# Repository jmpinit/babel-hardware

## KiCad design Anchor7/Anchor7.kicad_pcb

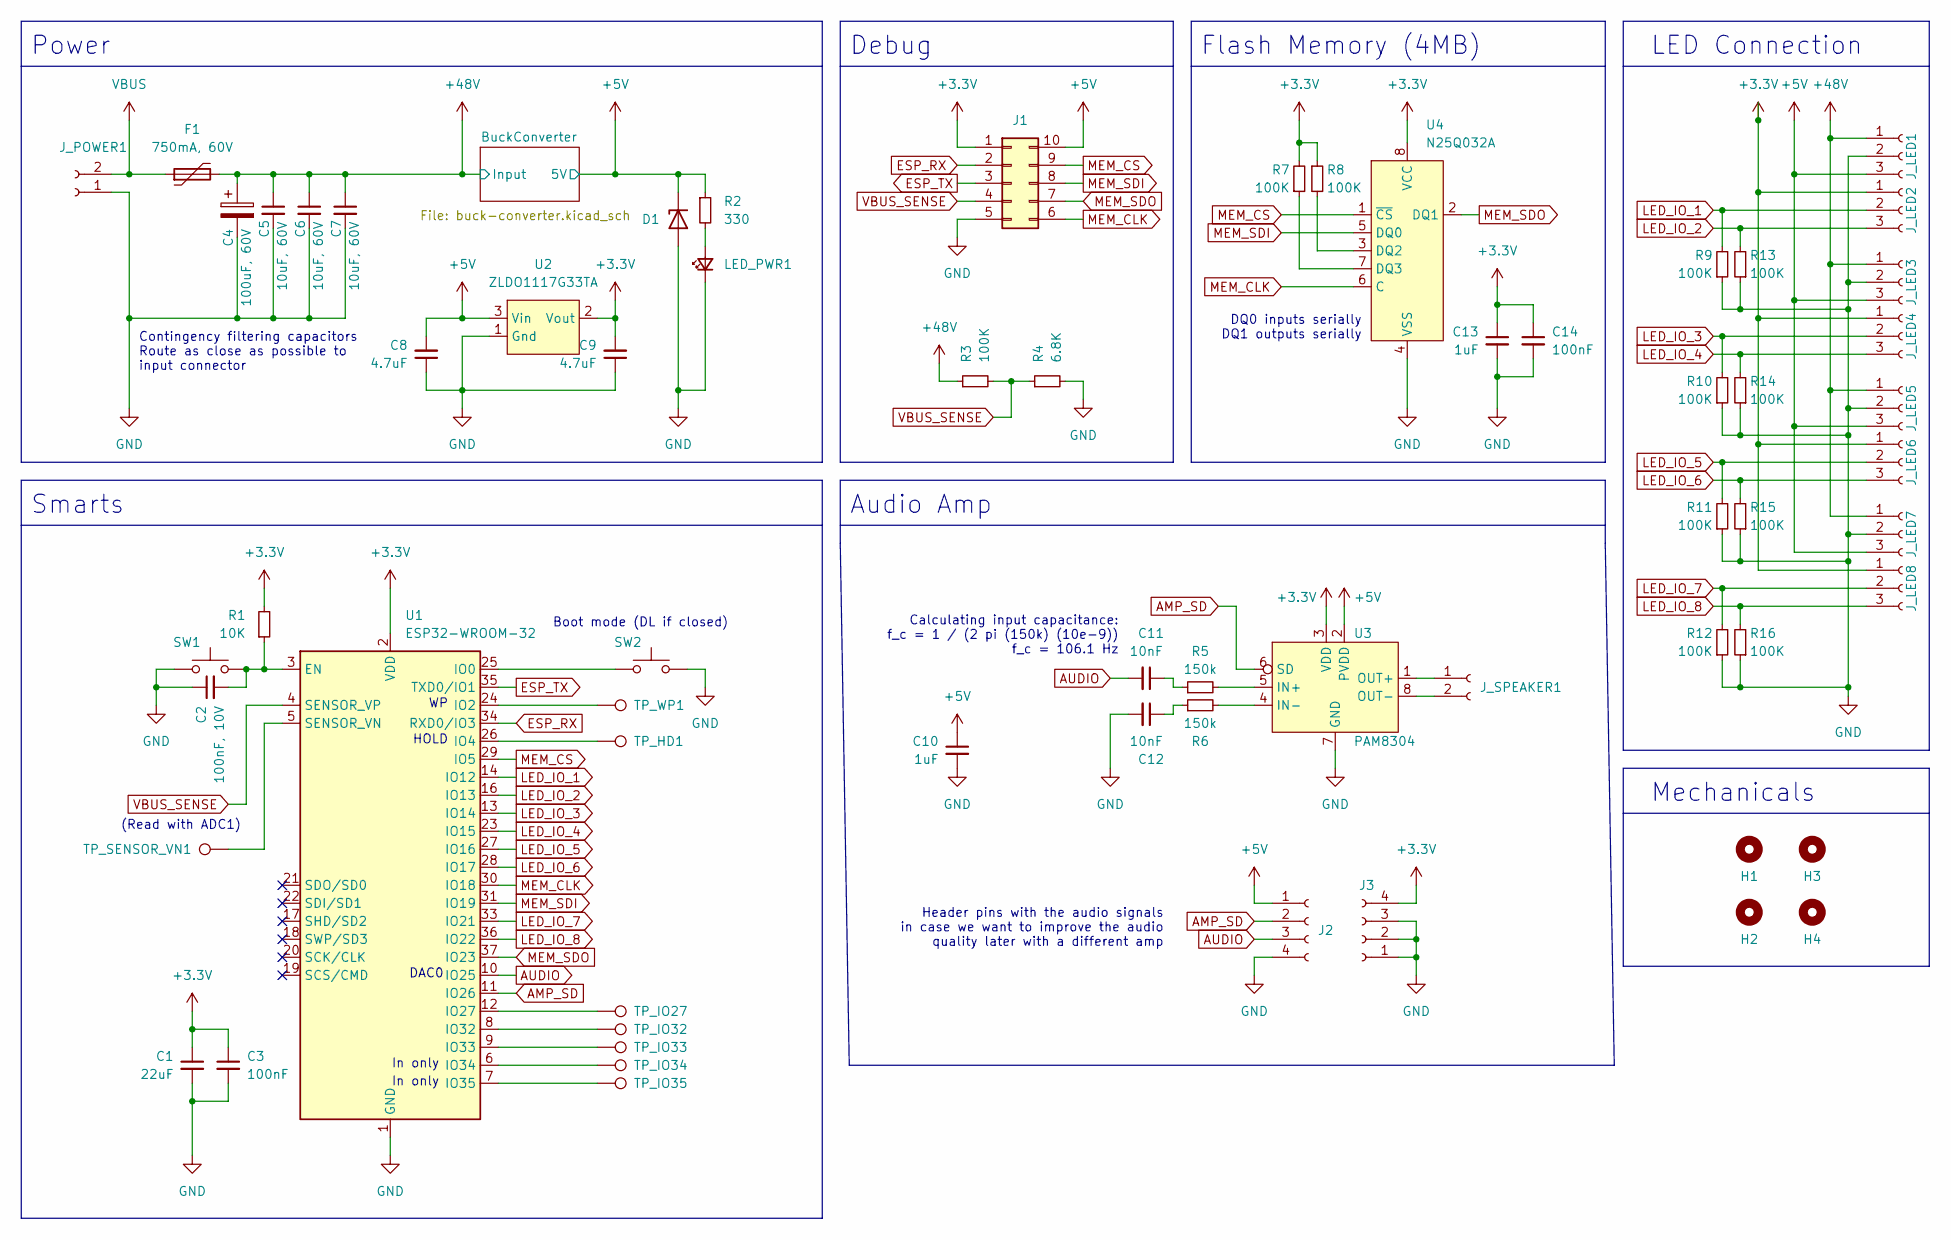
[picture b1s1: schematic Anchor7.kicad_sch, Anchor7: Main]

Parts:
C1: 22uF; C_0603_1608Metric; Digi-Key Part Number 1276-1274-2-ND
C2: 100nF, 10V; C_0402_1005Metric; Digi-Key Part Number 1276-1043-2-ND
C3, C14: 100nF; C_0402_1005Metric; Digi-Key Part Number 1276-1043-2-ND
C4: 100uF, 60V; CP_Radial_D8.0mm_P3.50mm
C5, C6, C7: 10uF, 60V; C_1206_3216Metric; Digi-Key Part Number 1276-7053-2-ND
C8, C9: 4.7uF; C_0603_1608Metric; Digi-Key Part Number 1276-1044-2-ND
C10, C13: 1uF; C_0603_1608Metric; Digi-Key Part Number 1276-1945-2-ND
C11, C12: 10nF; C_0402_1005Metric; Digi-Key Part Number 478-1114-2-ND
D1: 5.1V; SOT-23; Digi-Key Part Number 1727-2939-2-ND
F1: 750mA, 60V; Fuse_2920_7451Metric_Pad2.10x5.45mm_HandSolder; Digi-Key Part Number 507-1743-2-ND
H1, H2, H3, H4: MountingHole; MountingHole_3.2mm_M3
J1: Conn_02x05_Counter_Clockwise; Tag-Connect_TC2050-IDC-FP_2x05_P1.27mm_Vertical
J2, J3: Conn_01x04_Female; PinHeader_1x04_P2.54mm_Vertical
J_LED1, J_LED2, J_LED3, J_LED4, J_LED5, J_LED6, J_LED7, J_LED8: Conn_01x03_Female; PinHeader_1x03_P2.54mm_Vertical
J_POWER1: Conn_01x02_Female; Anchor_Power_2Pad
J_SPEAKER1: Conn_01x02_Female; PinHeader_1x02_P2.54mm_Vertical
LED_PWR1: LED_Small; LED_0402_1005Metric_Pad0.77x0.64mm_HandSolder
R1: 10K; R_0402_1005Metric; Digi-Key Part Number CR0402-JW-103GLFTR-ND
R2: 330; R_0402_1005Metric; Digi-Key Part Number 1292-WR04X331JTLTR-ND
R3, R7, R8, R9, R10, R11, R12, R13, R14, R15, R16: 100K; R_0402_1005Metric; Digi-Key Part Number 1292-WR04X104JTLTR-ND
R4: 6.8K; R_0402_1005Metric; Digi-Key Part Number 1292-WR04X682JTLTR-ND
R5, R6: 150k; R_0402_1005Metric; Digi-Key Part Number 1292-WR04X154JTLTR-ND
SW1, SW2: SW_Push; SW_SPST_PTS526; Digi-Key Part Number CKN12220-1-ND
TP_HD1: TestPoint; TestPoint_Pad_D1.5mm
TP_IO27, TP_IO32, TP_IO33, TP_IO34, TP_IO35: TestPoint; TestPoint_Pad_D1.5mm
TP_SENSOR_VN1: TestPoint; TestPoint_Pad_D1.5mm
TP_WP1: TestPoint; TestPoint_Pad_D1.5mm
U1: ESP32-WROOM-32
U2: ZLDO1117G33TA; SOT-223-3_TabPin2; Digi-Key Part Number ZLDO1117G33DITR-ND
U3: PAM8304; DFN-8-1EP_3x3mm_P0.65mm_EP1.55x2.4mm; Digi-Key Part Number PAM8304AYRDITR-ND
U4: N25Q032A; SOIC-8_3.9x4.9mm_P1.27mm; Digi-Key Part Number 1450-N25Q032A13ESC40FTR-ND

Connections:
+3V3: C1.1, C3.1, C9.2, C13.1, C14.1, J1.1, J3.4, J_LED2.1, J_LED4.1, J_LED6.1, J_LED8.1, R1.2, R7.2, R8.1, U1.2 (VDD), U2.2 (Vout), U3.3 (VDD), U4.8 (VCC)
+5V: C8.2, C10.1, D1.1 (K), J1.10, J2.1, J_LED1.3, J_LED3.3, J_LED5.3, J_LED7.3, R2.1, U2.3 (Vin), U3.2 (PVDD); also elsewhere on the board
+48V: C4.1, C5.1, C6.1, C7.1, F1.2, J_LED1.1, J_LED3.1, J_LED5.1, J_LED7.1, R3.1; also elsewhere on the board
AMP_SD: J2.2, U1.11 (IO26), U3.6 (SD)
AUDIO: C11.2, J2.3, U1.10 (IO25)
ESP_RX: J1.2, U1.34 (RXD0/IO3)
ESP_TX: J1.3, U1.35 (TXD0/IO1)
GND: C1.2, C2.1, C3.2, C4.2, C5.2, C6.2, C7.2, C8.1, C9.1, C10.2, C12.2, C13.2, C14.2, D1.2 (A), J1.5, J2.4, J3.1, J3.2, J3.3, J_LED1.2, J_LED3.2, J_LED5.2, J_LED7.2, J_POWER1.1, LED_PWR1.1 (K), R4.2, R9.1, R10.1, R11.1, R12.1, R13.1, R14.1, R15.1, R16.1, SW1.1, SW2.2, U1.1 (GND), U1.15 (GND), U1.38 (GND), U1.39 (GND), U2.1 (Gnd), U3.7 (GND), U4.4 (VSS); also elsewhere on the board
LED_IO_1: J_LED2.2, R9.2, U1.14 (IO12)
LED_IO_2: J_LED2.3, R13.2, U1.16 (IO13)
LED_IO_3: J_LED4.2, R10.2, U1.13 (IO14)
LED_IO_4: J_LED4.3, R14.2, U1.23 (IO15)
LED_IO_5: J_LED6.2, R11.2, U1.27 (IO16)
LED_IO_6: J_LED6.3, R15.2, U1.28 (IO17)
LED_IO_7: J_LED8.2, R12.2, U1.33 (IO21)
LED_IO_8: J_LED8.3, R16.2, U1.36 (IO22)
MEM_CLK: J1.6, U1.30 (IO18), U4.6 (C)
MEM_CS: J1.9, U1.29 (IO5), U4.1 (~CS)
MEM_SDI: J1.8, U1.31 (IO19), U4.5 (DQ0)
MEM_SDO: J1.7, U1.37 (IO23), U4.2 (DQ1)
unnamed: C2.2, R1.1, SW1.2, U1.3 (EN)
unnamed: C11.1, R5.1
unnamed: C12.1, R6.1
unnamed: J_SPEAKER1.1, U3.1 (OUT+)
unnamed: J_SPEAKER1.2, U3.8 (OUT-)
unnamed: LED_PWR1.2 (A), R2.2
unnamed: R5.2, U3.5 (IN+)
unnamed: R6.2, U3.4 (IN-)
unnamed: R7.1, U4.7 (DQ3)
unnamed: R8.2, U4.3 (DQ2)
unnamed: SW2.1, U1.25 (IO0)
unnamed: TP_HD1.1, U1.26 (IO4)
unnamed: TP_IO27.1, U1.12 (IO27)
unnamed: TP_IO32.1, U1.8 (IO32)
unnamed: TP_IO33.1, U1.9 (IO33)
unnamed: TP_IO34.1, U1.6 (IO34)
unnamed: TP_IO35.1, U1.7 (IO35)
unnamed: TP_SENSOR_VN1.1, U1.5 (SENSOR_VN)
unnamed: TP_WP1.1, U1.24 (IO2)
VBUS: F1.1, J_POWER1.2
VBUS_SENSE: J1.4, R3.2, R4.1, U1.4 (SENSOR_VP)

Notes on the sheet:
Header pins with the audio signals in case we want to improve the audio quality later with a different amp
Power
(Read with ADC1)
Smarts
Audio Amp
HOLD
Mechanicals
Contingency filtering capacitors Route as close as possible to input connector
In only
LED Connection
Flash Memory (4MB)
DAC0
Debug
DQ0 inputs serially DQ1 outputs serially
Boot mode (DL if closed)
Calculating input capacitance: f_c = 1 / (2 pi (150k) (10e-9)) f_c = 106.1 Hz

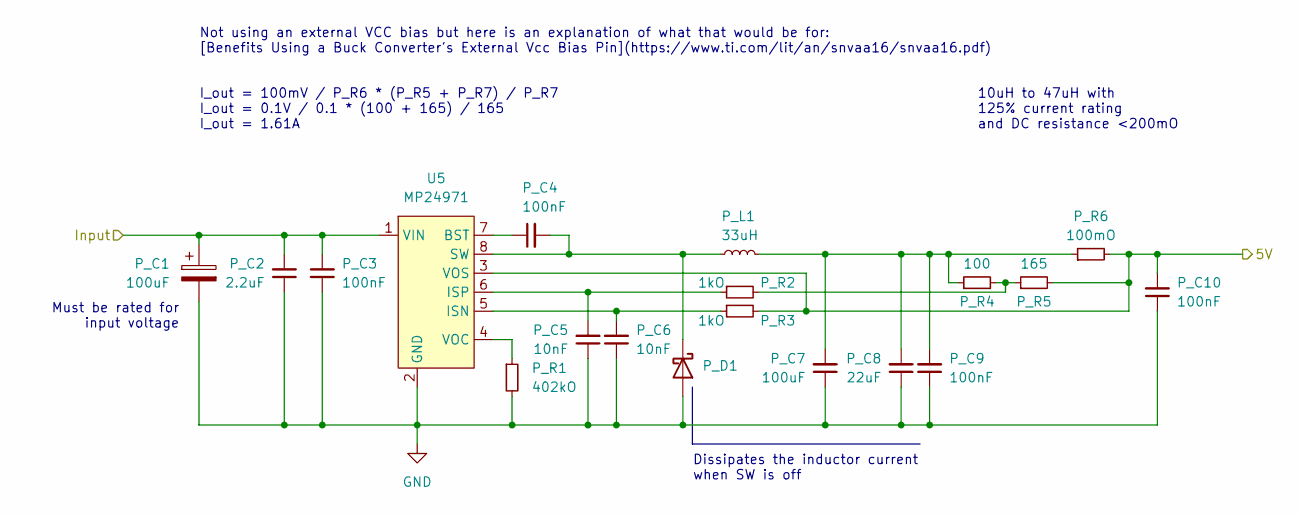
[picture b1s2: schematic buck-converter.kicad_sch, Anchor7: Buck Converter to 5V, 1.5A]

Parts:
P_C1: 100uF; CP_Radial_D8.0mm_P3.50mm; Digi-Key Part Number 1189-3041-ND
P_C2: 2.2uF; C_1206_3216Metric; Digi-Key Part Number 445-181654-2-ND
P_C3: 100nF; C_0805_2012Metric; Digi-Key Part Number 399-C0805C104KMREC7210TR-ND
P_C4, P_C9, P_C10: 100nF; C_0402_1005Metric; Digi-Key Part Number 1276-1004-2-ND
P_C5, P_C6: 10nF; C_0402_1005Metric; Digi-Key Part Number 478-04025C103MAT2ATR-ND
P_C7: 100uF; C_1210_3225Metric; Digi-Key Part Number 1276-1092-2-ND
P_C8: 22uF; C_0805_2012Metric; Digi-Key Part Number 490-10511-2-ND
P_D1: D_Schottky; D_SMA; Digi-Key Part Number 641-1102-2-ND
P_L1: 33uH; L_Taiyo-Yuden_NS-125xx; Digi-Key Part Number NS12555T330MN
P_R1: 402kO; R_0402_1005Metric; Digi-Key Part Number RMCF0402FT402KTR-ND
P_R2, P_R3: 1kO; R_0402_1005Metric; Digi-Key Part Number P1.0KJTR-ND
P_R4: 100; R_0402_1005Metric; Digi-Key Part Number CR0402-JW-101GLFTR-ND
P_R5: 165; R_0402_1005Metric; Digi-Key Part Number RMCF0402FT165RTR-ND
P_R6: 100mO; R_2512_6332Metric; Digi-Key Part Number CSRN2512FKR100TR-ND
U5: MP24971; SOIC-8-1EP_3.9x4.9mm_P1.27mm_EP2.29x3mm_ThermalVias; Digi-Key Part Number MP24971DN-LF-Z

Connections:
+5V: P_C10.2, P_R3.2, P_R5.2, P_R6.2, U5.3 (VOS); also elsewhere on the board
+48V: P_C1.1, P_C2.2, P_C3.2, U5.1 (VIN); also elsewhere on the board
GND: P_C1.2, P_C2.1, P_C3.1, P_C5.1, P_C6.1, P_C7.1, P_C8.1, P_C9.1, P_C10.1, P_D1.2 (A), P_R1.2, U5.2 (GND), U5.9 (GND); also elsewhere on the board
unnamed: P_C4.1, U5.7 (BST)
unnamed: P_C4.2, P_D1.1 (K), P_L1.1, U5.8 (SW)
unnamed: P_C5.2, P_R2.1, U5.6 (ISP)
unnamed: P_C6.2, P_R3.1, U5.5 (ISN)
unnamed: P_C7.2, P_C8.2, P_C9.2, P_L1.2, P_R4.1, P_R6.1
unnamed: P_R1.1, U5.4 (VOC)
unnamed: P_R2.2, P_R4.2, P_R5.1

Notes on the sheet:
10uH to 47uH with 125% current rating and DC resistance <200mO
Not using an external VCC bias but here is an explanation of what that would be for: [Benefits Using a Buck Converter's External Vcc Bias Pin](https://www.ti.com/lit/an/snvaa16/snvaa16.pdf)
Must be rated for input voltage
Dissipates the inductor current when SW is off
I_out = 100mV / P_R6 * (P_R5 + P_R7) / P_R7 I_out = 0.1V / 0.1 * (100 + 165) / 165 I_out = 1.61A

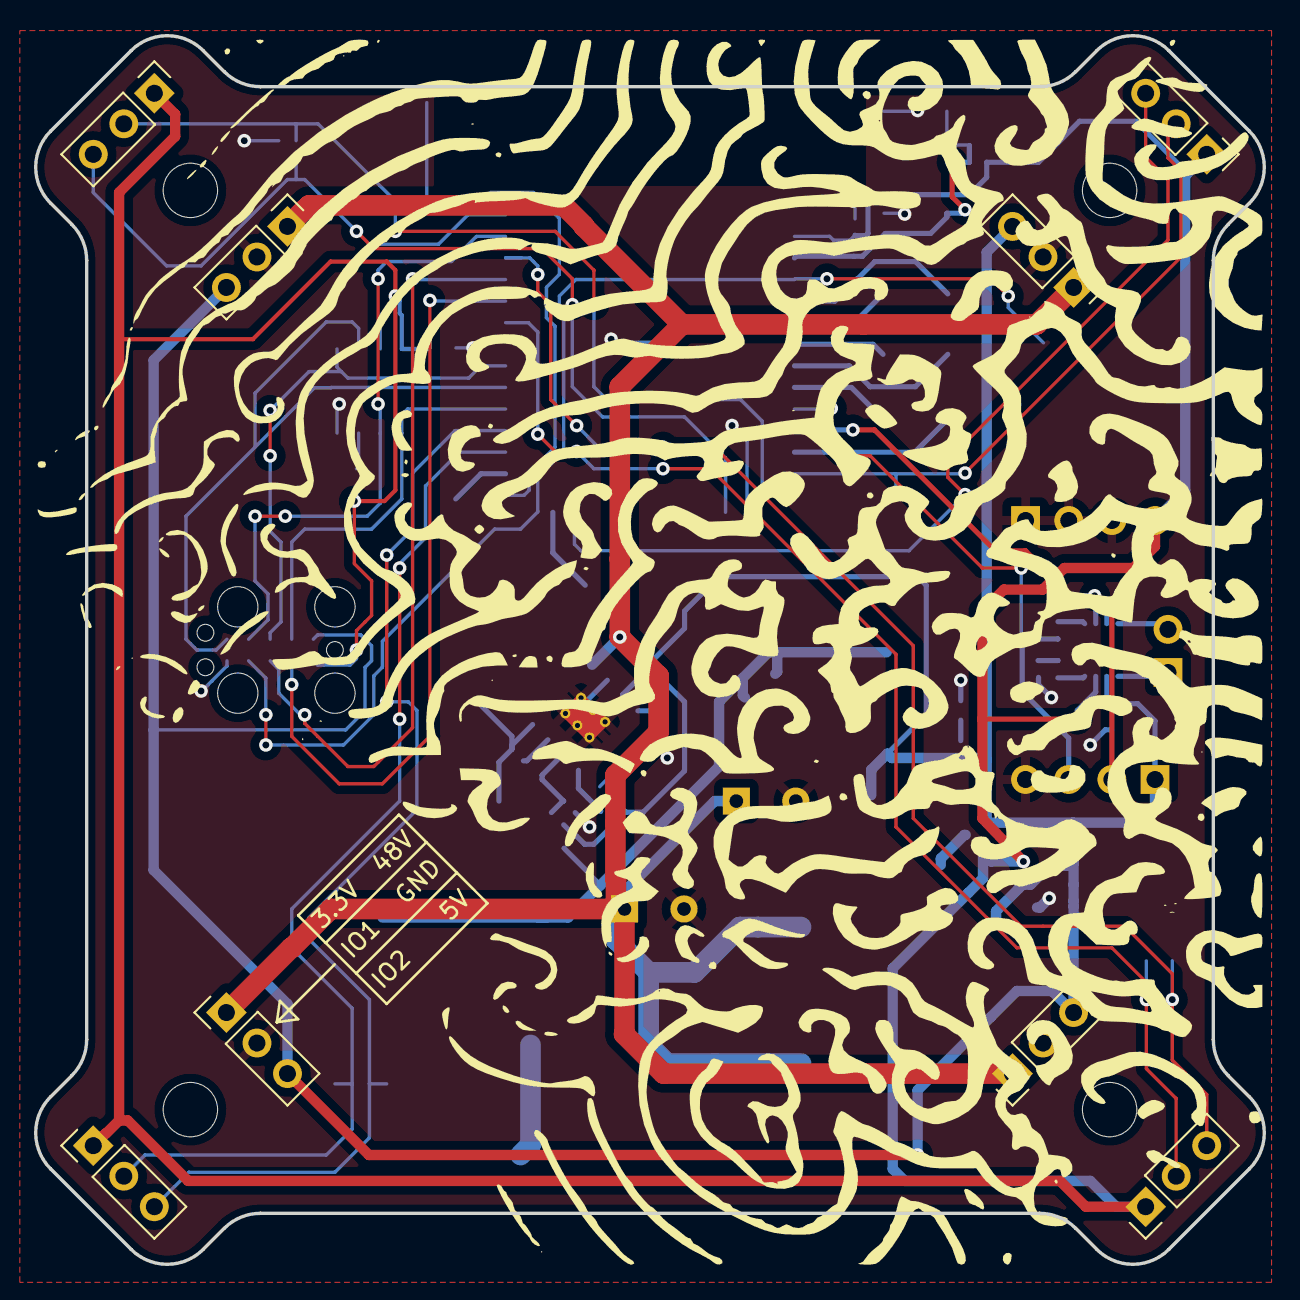
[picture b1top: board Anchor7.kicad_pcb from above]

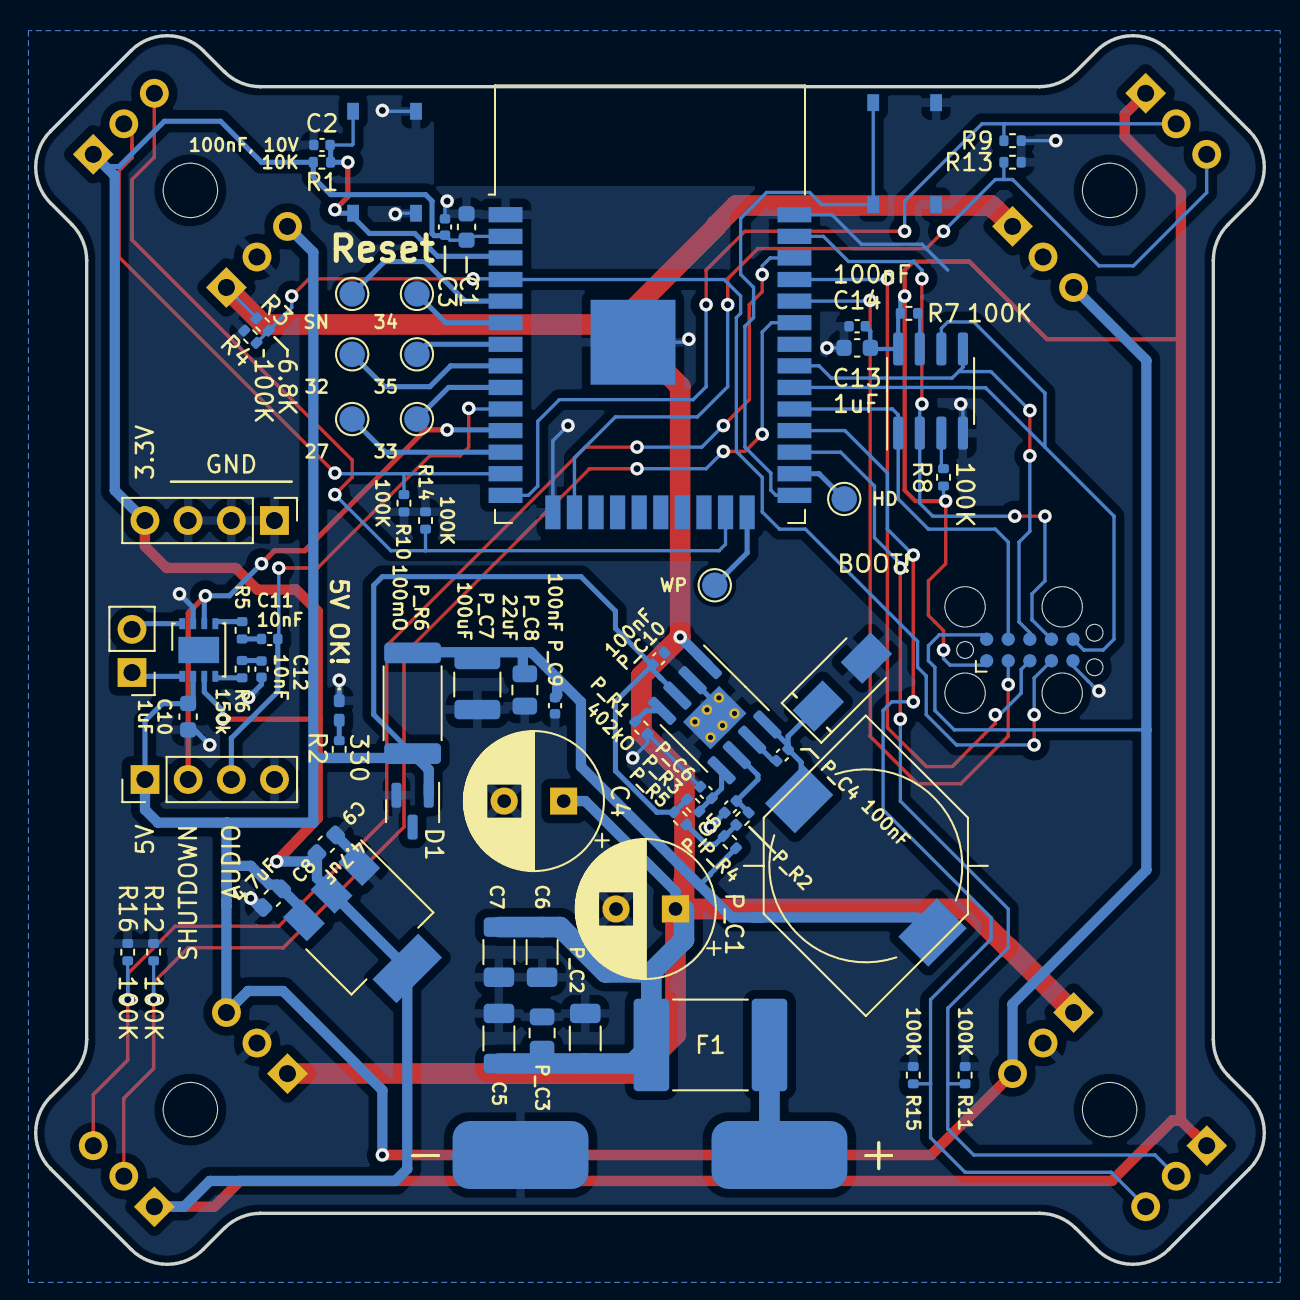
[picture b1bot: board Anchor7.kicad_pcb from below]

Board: 2 copper layers, 72.3 x 72.3 mm, 83 parts (75 on the bottom side), 48 nets.

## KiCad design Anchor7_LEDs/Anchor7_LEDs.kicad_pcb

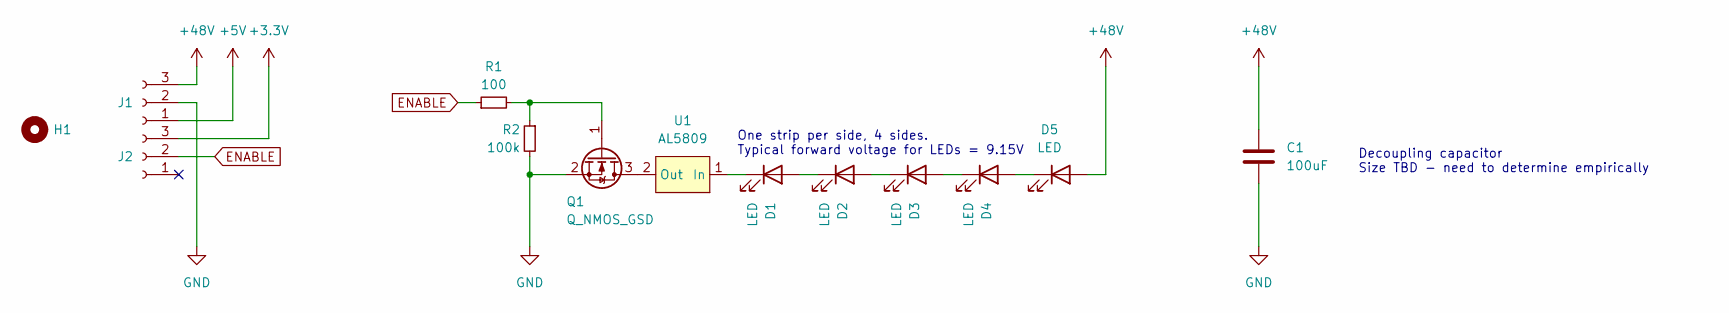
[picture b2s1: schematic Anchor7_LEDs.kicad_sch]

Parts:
C1: 100uF; C_0805_2012Metric
D1, D2, D3, D4, D5: LED; LED_PLCC_2835_Handsoldering; Digi-Key Part Number 2138-JK2835BWT-W-H40EC0000-N0000001TR-ND
H1: MountingHole; MountingHole_3.5mm
J1, J2: Conn_01x03_Female; PinHeader_1x03_P2.54mm_Vertical
Q1: Q_NMOS_GSD; SOT-723; Digi-Key Part Number NTK3134NT1G
R1: 100; R_0402_1005Metric
R2: 100k; R_0402_1005Metric
U1: AL5809; D_PowerDI-123; Digi-Key Part Number AL5809-100P1-7DITR-ND

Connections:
+3V3: J2.3
+5V: J1.1
+48V: C1.2, D5.2 (A), J1.3
ENABLE: J2.2, R1.1
GND: C1.1, J1.2, Q1.2 (S), R2.2
unnamed: D1.1 (K), U1.1 (In)
unnamed: D1.2 (A), D2.1 (K)
unnamed: D2.2 (A), D3.1 (K)
unnamed: D3.2 (A), D4.1 (K)
unnamed: D4.2 (A), D5.1 (K)
unnamed: Q1.1 (G), R1.2, R2.1
unnamed: Q1.3 (D), U1.2 (Out)

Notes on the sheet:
One strip per side, 4 sides. Typical forward voltage for LEDs = 9.15V
Decoupling capacitor Size TBD - need to determine empirically

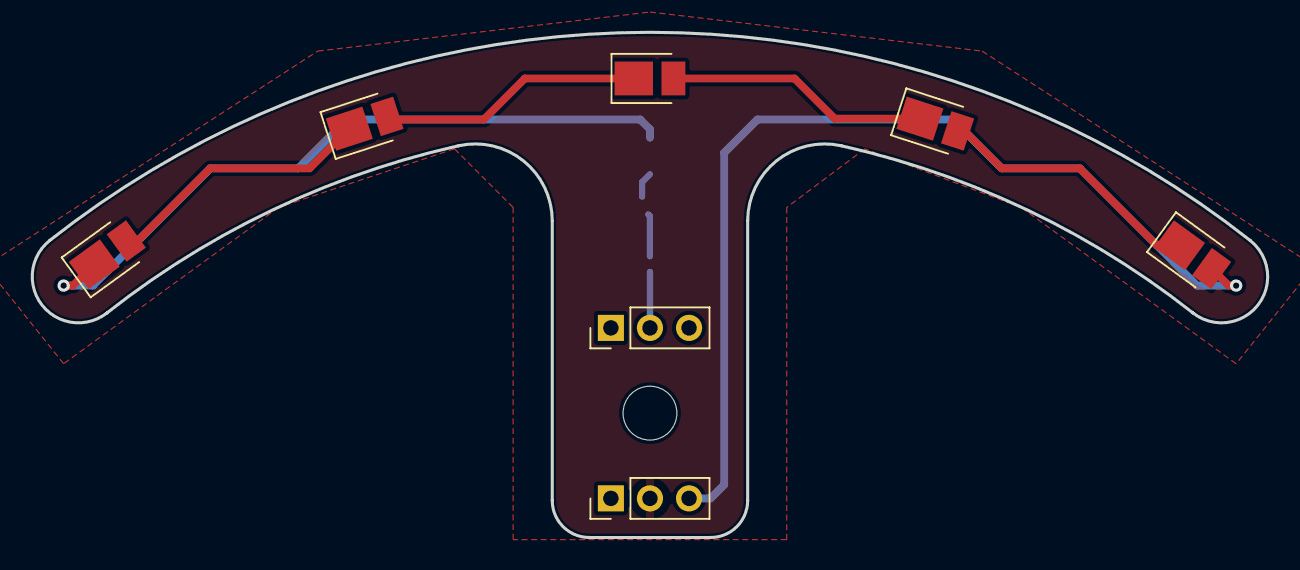
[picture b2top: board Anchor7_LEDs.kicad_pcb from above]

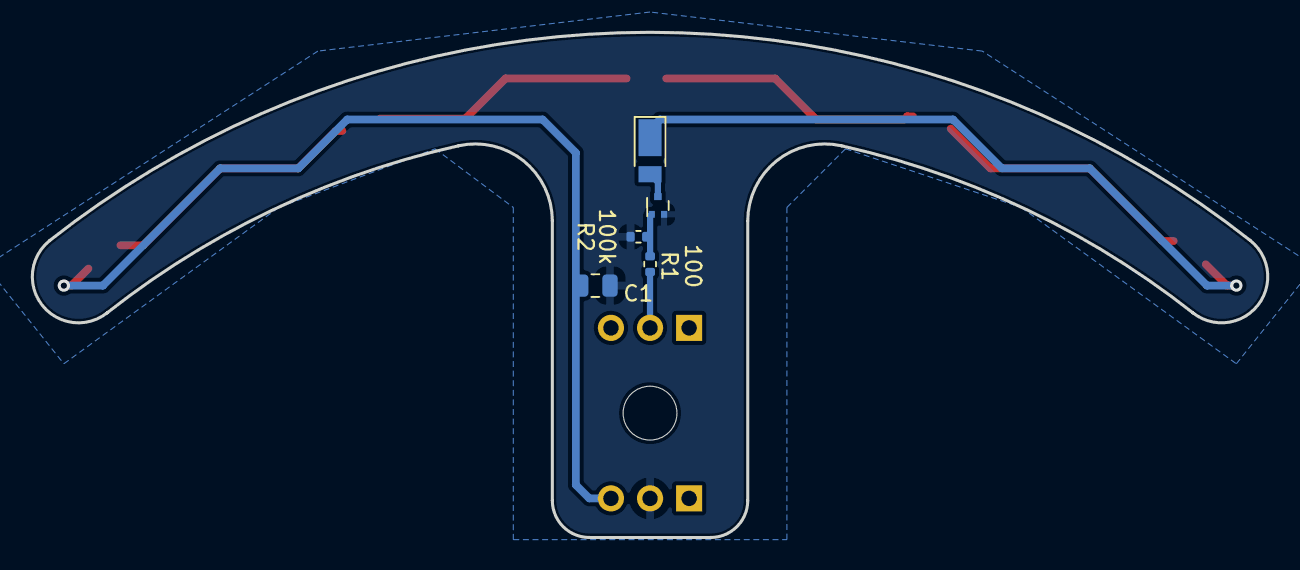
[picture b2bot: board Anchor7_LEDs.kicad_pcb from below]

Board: 2 copper layers, 80.3 x 32.8 mm, 13 parts (5 on the bottom side), 10 nets.

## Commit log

2023-08-23 Dump
